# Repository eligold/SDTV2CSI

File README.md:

# ADV7280A-M Pi Analog Video to MIPI CSI-2 Hardware

<br>

<br>

<br>

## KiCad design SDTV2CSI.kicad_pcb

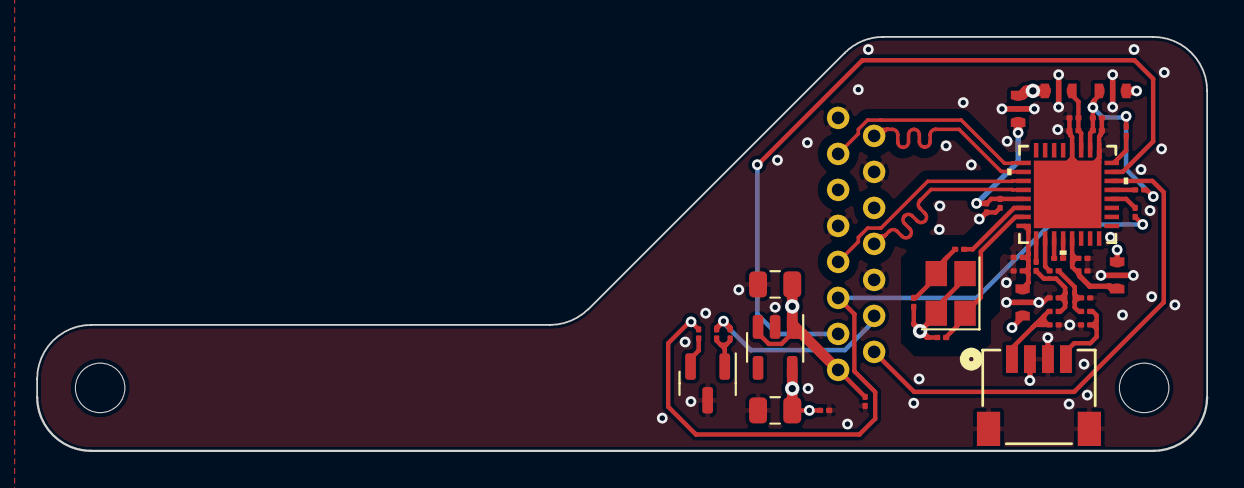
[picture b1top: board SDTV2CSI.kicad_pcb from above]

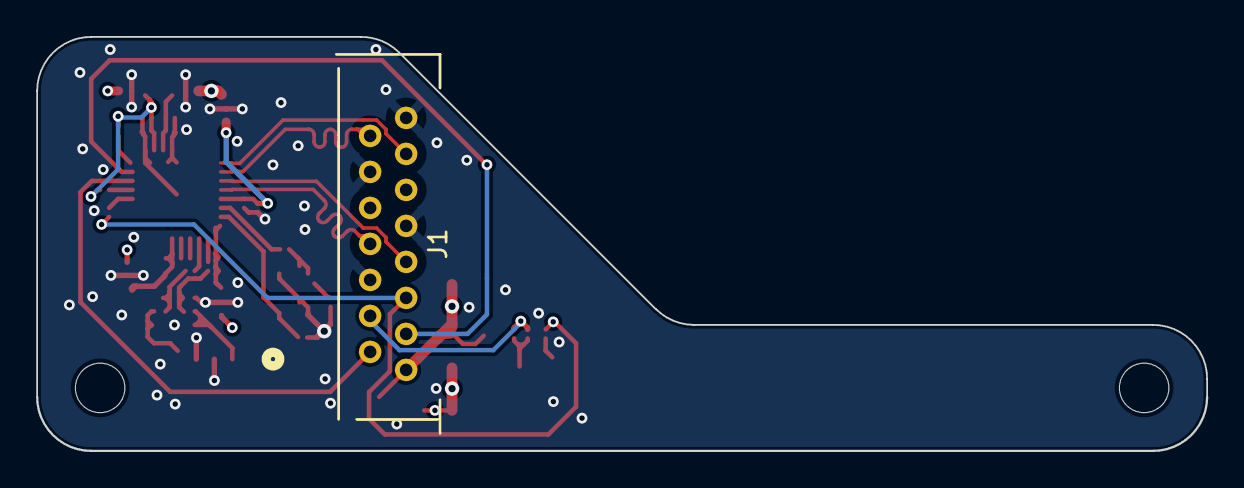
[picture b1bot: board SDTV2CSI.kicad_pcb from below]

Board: 4 copper layers, 65.0 x 23.0 mm, 44 parts (2 on the bottom side), 32 nets.

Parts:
C1, C3, C5, C7, C9: 0.01μF; R_0201_0603Metric
C2, C4, C6, C8, C10, C11, C12, C13: 0.1μF; R_0201_0603Metric
C14, C15: 100μF; C_0805_2012Metric
C16, C17: 20pF; R_0201_0603Metric
D1: 3VWM; R_0201_0603Metric
D2: 2VWM; R_0201_0603Metric
D3, D4: TVS; R_0201_0603Metric
D5: LED_Dual_AAK; SOT-23
F1, F2, F3, F4, F5: LC(Pi); MEM1608P25R0T001
J1: SFW15R-1STE1LF; 528061510
J2: SM04B-SRSS-TB; SM04B-SRSS-TB_JST
P1: Pi Zero; PIZERO
R1, R3: 24; R_0201_0603Metric
R2, R4: 51; R_0201_0603Metric
R5, R6, R7: 4.7k; R_0201_0603Metric
R8, R9, R10: 560; R_0201_0603Metric
R11: 220; R_0201_0603Metric
U1: ADV7280AWBCPZ-M; CP_32_12_ADI
U2: TLV75718; SOT-23-5
Y1: 28.63636MHz; Crystal_SMD_SeikoEpson_FA238-4Pin_3.2x2.5mm

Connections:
+1V8: C15.2, D2.1 (K), F2.1, F3.1, F4.1, F5.1, U2.5 (OUT)
+3V3: C14.2, D1.1 (K), F1.1, J1.1, U2.1 (IN), U2.3 (EN)
AVDD: C9.2, C10.1, F5.3, U1.21 (AVDD)
CD0+: J1.13, U1.9 (D0P)
CD0-: J1.14, U1.10 (D0N)
CLK+: J1.7, U1.11 (CLKP)
CLK-: J1.8, U1.12 (CLKN)
CSCL: J1.3, U1.31 (SCLK)
CSDA: J1.2, U1.30 (SDATA)
DVDD: C5.2, C6.1, F3.3, U1.3 (DVDD)
DVDDIO: C1.2, C2.1, F1.3, R6.1, R7.1, U1.2 (DVDDIO)
GND: C1.1, C2.2, C3.1, C4.2, C5.1, C6.2, C7.1, C8.2, C9.1, C10.2, C14.1, C15.1, C16.1, C17.1, D1.2 (A), D2.2 (A), D3.2 (A), D4.2 (A), D5.3 (K), F1.2_4, F2.2_4, F3.2_4, F4.2_4, F5.2_4, J1.6, J1.9, J1.12, J1.15, J2.2, J2.3, J2.5, J2.6, R2.1, R4.1, U1.1 (DGND), U1.4 (DGND), U1.33 (EPAD), U2.2 (GND), Y1.2, Y1.4
LED_EN: J1.4, R9.2, R10.2
MVDD: C3.2, C4.1, F2.3, U1.13 (MVDD)
unnamed: C11.2, R1.2, R2.2
unnamed: C12.2, R3.2, R4.2
unnamed: C13.1, U1.20 (VREFN)
unnamed: C13.2, U1.19 (VREFP)
unnamed: C17.2, R8.1, Y1.3
unnamed: D5.1 (A1), R9.1, R10.1
unnamed: D5.2 (A2), R11.1
unnamed: R5.1, U1.28 (*RESET)
unnamed: R6.2, U1.32 (*PWRDWN)
unnamed: R7.2, U1.29 (ALSB)
PVDD: C7.2, C8.1, F4.3, U1.16 (PVDD)
PWR_EN: J1.5, R5.2, R11.2
XN: C16.2, U1.15 (XTALN), Y1.1
XP: R8.2, U1.14 (XTALP)
video1: C11.1, U1.17 (AIN1)
video2: C12.1, U1.18 (AIN2)
video_in1: D3.1 (K), J2.1, R1.1
video_in2: D4.1 (K), J2.4, R3.1

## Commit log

2024-08-20 init
2024-08-23 update and considering losing poe for waveshare OTS
2024-08-24 working on converting back to 0201
2024-08-25 will remove PoE components commit for posterity
2025-03-17 updating for GitHub
2025-03-31 Create LICENSE
2025-04-06 Update README.md to fix syntax issue
2025-05-14 latest iteration with smaller filters and bigger more secure footprint
2025-05-14 new images having passed DFM checks
